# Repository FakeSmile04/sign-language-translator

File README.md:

# sign-language-translator
AI-based Sign Language Translator Using Electromyography

## Version 0.5
- Now uses Mosquitto as the MQTT broker (Mosquitto is required to run the program)
- Uploaded latest version of the Arduino Sketch that now has config mode using simple webpage in AP
- Uploaded Flutter Project Directory pertaining to mobile interface
- Uploaded stable release .apk file of the mobile interface for Android phones

Notes:
- Python backend isn't finalised yet
- PCB sketch project files and other related files aren't uploaded yet

## Version 0.2
- Implemented MQTT as the method of sending data from ESP32 to app.py
- Removed codes related to serial method
- Uploaded an updated version of Arduino sketch installed in ESP32 for EMG data collection
- Added basic stylings for the webpage to make it looks nicer
- Cleaned out the file strcture of the whole repository

Notes:
- WiFi credentials are in the sketch and has to be reuploaded to ESP32 each time it is used
- ESP32 and the PC doesn't need to be in same network in theory, not tried yet

Future Plans:
- Implement a better ML model for sign prediction
- Test the program with new sensor circuit setup

## Version 0.1.2
- Added AI prediction model and TTS capability on the Websocket version
- Recommended to use Chrome to run index.html

Issues and Future Plans:
- Implement port fowarding so it can be used online (to port 8000)
- Look into possibility on making the output as close to real-time as possible
- Test the program with proper EMG sensors once worked

## Version 0.1.1

- Added another version of the program that doesn't use XAMPP, instead serves the webpage directly from Python due to issues implementing WebSocket in XAMPP environment
- Tested out some basic TTS functionalities to read out the page's **header**

Issues and Future Plans:
- The values presented on the webpage aren't still in real time
- Implement AI model to read the signals and translate it into words
- Expand TTS functionality to read the words

## Version 0.1

Developed on XAMPP Local Web Server

Notes:
- data.json and homepage.php has to be put inside the htdocs folder in XAMPP's directory
- The ESP32 Microcontroller is connected to the PC on port COM9 with appropiate driver (port used can be changed in bridge.py)

Current Progress:
The program is now able to read signals from the EMG sensor, process it and sends it to a webpage to display the result

Current Issues:
The display values aren't in real-time

Future Plans:
- Move to WebSocket Server for real-time value display
- Add AI TTS to read what's on the webpage
- Implement AI model to read the signals and translate it into words

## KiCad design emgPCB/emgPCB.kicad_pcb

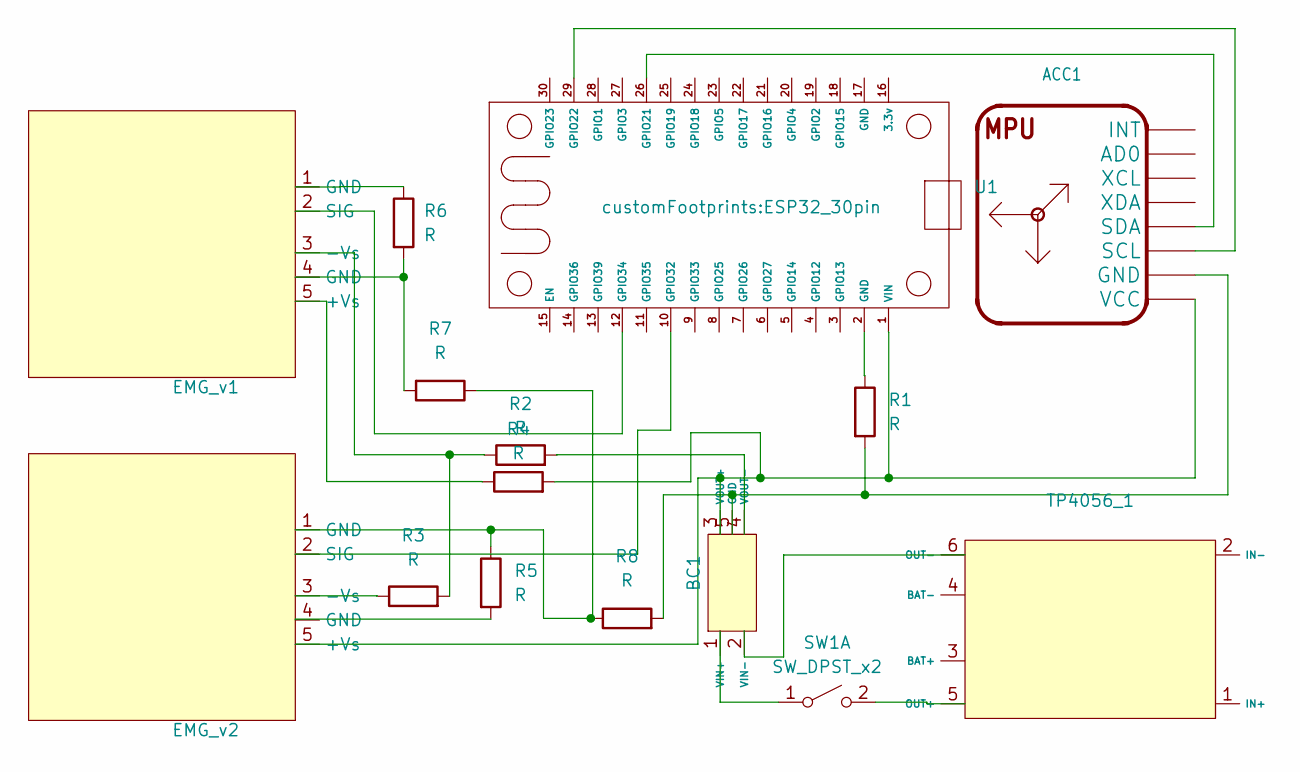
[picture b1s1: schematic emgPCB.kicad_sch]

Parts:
ACC1: GY-521
BC1: BC
EMG_v1, EMG_v2: EMG sensor
R1, R2, R3, R4, R5, R6, R7, R8: R; Jumper-Wire_8mm_Blue
SW1: SW_DPST_x2; switch
TP4056_1: TP4056-Module
U1: ESP32_30pin

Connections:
unnamed: ACC1.GND, BC1.5 (GND), R1.2, R8.2
unnamed: BC1.1 (VIN+), SW1.1 (A)
unnamed: BC1.2 (VIN-), TP4056_1.6 (OUT-)
unnamed: ACC1.VCC, BC1.3 (VOUT+), EMG_v2.5 (+Vs), R4.2, U1.1 (VIN)
unnamed: BC1.4 (VOUT-), R2.2
unnamed: EMG_v1.5 (+Vs), R4.1
unnamed: EMG_v1.3 (-Vs), R2.1, R3.2
unnamed: EMG_v1.1 (GND), R6.1
unnamed: EMG_v1.4 (GND), R6.2, R7.2
unnamed: EMG_v1.2 (SIG), U1.12 (GPIO34)
unnamed: EMG_v2.3 (-Vs), R3.1
unnamed: EMG_v2.1 (GND), R5.1, R7.1, R8.1
unnamed: EMG_v2.4 (GND), R5.2
unnamed: EMG_v2.2 (SIG), U1.10 (GPIO32)
unnamed: R1.1, U1.2 (GND)
unnamed: SW1.2 (B), TP4056_1.5 (OUT+)
unnamed: ACC1.SDA, U1.26 (GPIO21)
unnamed: ACC1.SCL, U1.29 (GPIO22)

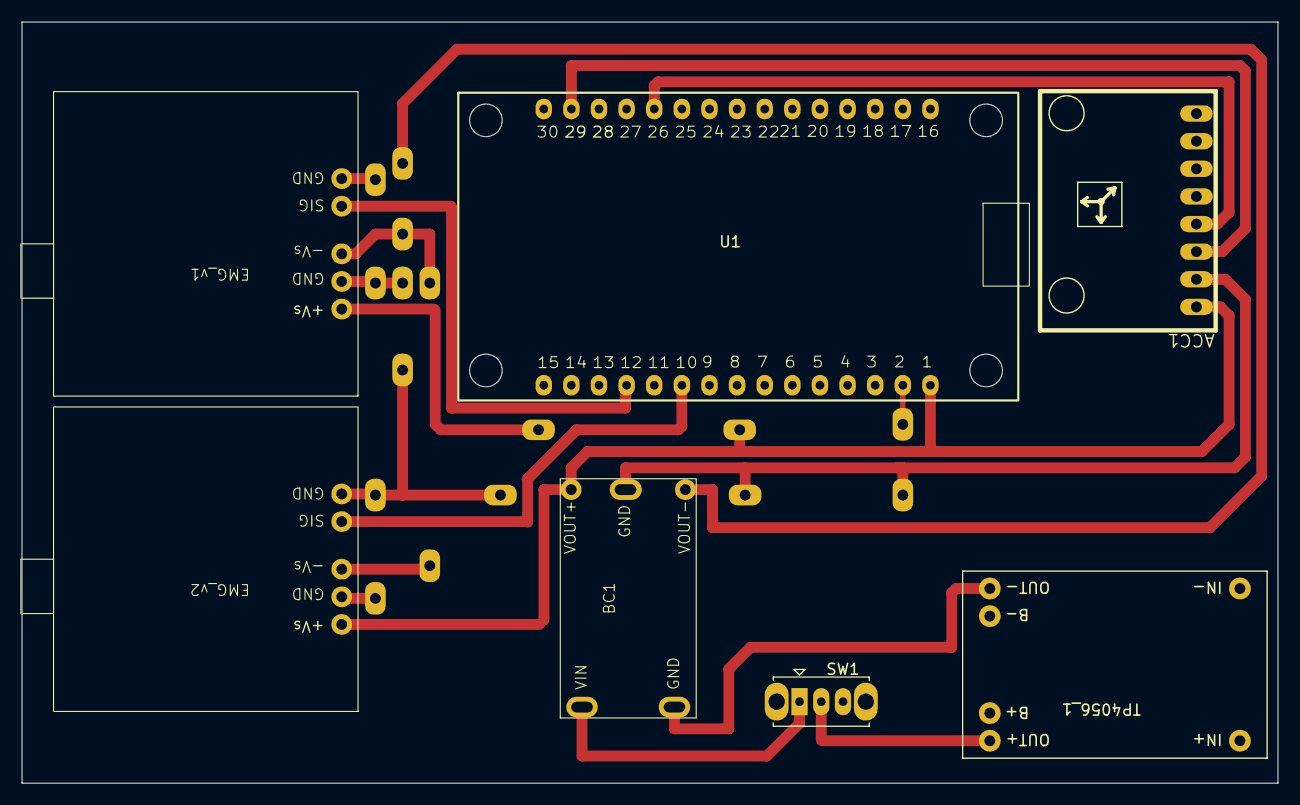
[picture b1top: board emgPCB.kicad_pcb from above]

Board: 2 copper layers, 115.5 x 70.0 mm, 15 parts (0 on the bottom side), 18 nets.

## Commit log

2025-04-10 base files for the web program
    bridge.py - Python program to process the input from sensor and send it to the webpage
    homepage.php - a PHP + HTML + JavaScript file that receives input from the sensor and displays it
    Issues: The displayed value isn't close to real-time values produced by the Python code
2025-04-10 Update README.md
    Add extensive details of the program alongside some details
2025-04-15 Websocket implementations
    Changed codes that uses Websocket and a Python local server instead of XAMPP
2025-04-15 Update README.md
    Version 0.1.1 description
2025-04-16 updated websocket with AI model and TTS
2025-04-16 Update README.md
    version 0.1.2 details
2025-05-03 Updated files with MQTT
2025-05-03 Update README.md
    Version 0.2 description
2025-05-03 V0.1 reupload in one folder
2025-12-13 Version 0.5 alongside file restructuring
2025-12-13 Update README with version 0.5 information
    Added version 0.5 details including Mosquitto, Arduino Sketch, Flutter Project, and .apk file.
2025-12-15 Add files via upload
    Added the v0.5 application for sending the prediction to mobile app/web app
2026-01-14 upload PCB design files
    upload KiCad project files for finalized PCB design
